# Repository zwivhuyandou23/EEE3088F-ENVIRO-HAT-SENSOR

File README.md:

### ENVIRO-SENSING-HAT

## Name
ENVIRO-SENSING-HAT

## Description

The ENVIRO-SENSING-HAT is a design project that incorporates a Light Dependent Resistor (LDR) and a temperature sensor with an onboard FTDI IC chip. This HAT (Hardware Attached on Top) is designed to provide environmental sensing capabilities for various applications.

## Features

- Light Dependent Resistor (LDR) for monitoring light levels
- Temperature sensor for measuring ambient temperature
- Onboard FTDI IC chip for communication and data transfer
- Customizable and programmable for different applications

## Project Scenarios

The ENVIRO-SENSING-HAT can be used in various scenarios to monitor and analyze environmental conditions. Some of the key scenarios include:

1. **Fire Detection:** The HAT can monitor light levels and temperature. In the case of a fire, the light levels and temperature will rise to extreme levels. The HAT can be integrated into a fire detection system where it triggers an alarm if the levels exceed a certain threshold.

2. **Weather Station:** By monitoring light levels and temperature, the HAT can be used as part of a weather station for weather forecasting purposes. It can collect data over time to analyze weather patterns and provide valuable insights.

3. **Greenhouse Control System:** In a greenhouse, the HAT can be integrated into a control system to monitor environmental conditions. It can detect light levels and temperature to determine the optimal conditions for plant growth. The HAT can control fans and irrigation systems based on the detected environmental conditions.

## Installation
To access some of the contents on the repo you will need kicad to open the project PCB, Schematics designs and an IDE that supports C programming

## Usage

To use the ENVIRO-SENSING-HAT, you need to connect it to a compatible development board or microcontroller. You can refer to the documentation or specifications of your specific board to understand how to interface with the HAT. Additionally, you may need to install any required libraries or drivers for proper functionality.

Once the HAT is properly connected, you can develop software or write code to read data from the LDR and temperature sensor, and utilize the onboard FTDI IC chip for communication and data transfer.

## Authors and acknowledgment

Zwivhuya Ndou, Sivuyile Nose, Talifhani Nemaangani

## Contributing

Contributions to the ENVIRO-SENSING-HAT project are welcome! If you have any ideas, bug fixes, or improvements, please follow the guidelines outlined in the [CONTRIBUTING.md](CONTRIBUTING.md) file.

## License

The ENVIRO-SENSING-HAT project is licensed under the MIT License. See the [LICENSE](LICENSE.md) file for more information.

## Project status
Requirements Identifying

## Contact

If you have any questions or inquiries about the ENVIRO-SENSING-HAT project, feel free to contact us at [CONTACT](Zwivhuya Ndou, Sivuyile Nose, Talifhani Nemaangani).

Thank you for your interest in the ENVIRO-SENSING-HAT project!

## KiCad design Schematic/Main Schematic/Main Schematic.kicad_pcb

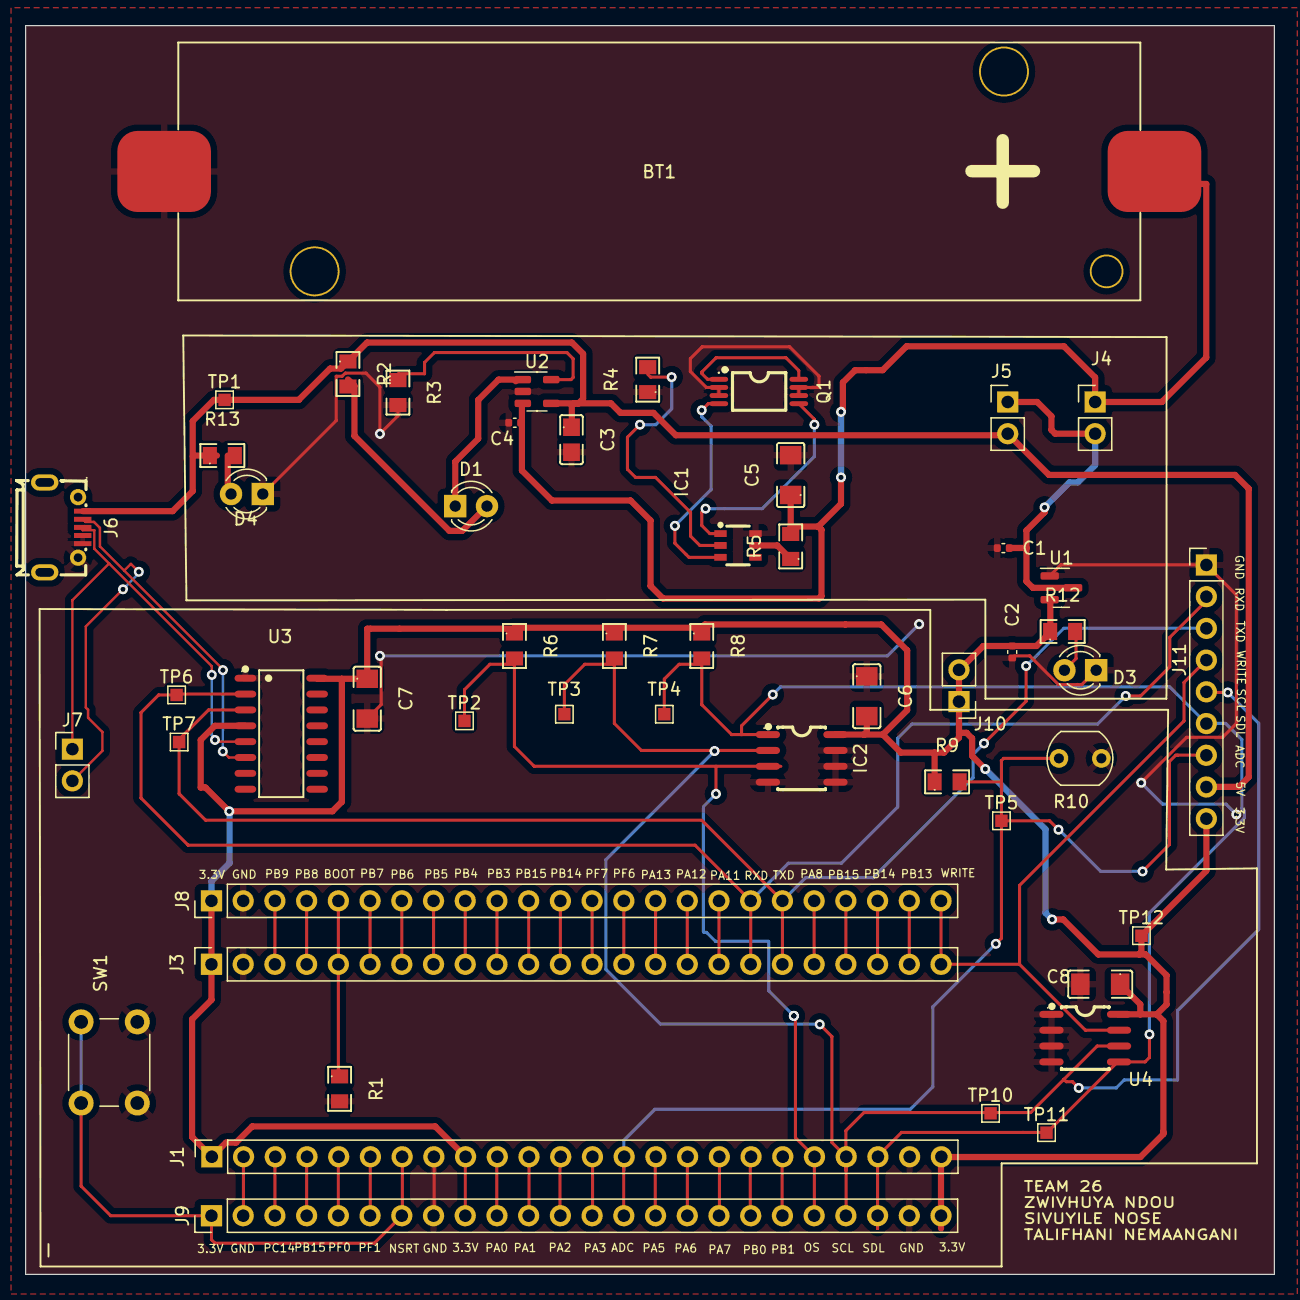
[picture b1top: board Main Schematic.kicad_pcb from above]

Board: 2 copper layers, 100.0 x 100.0 mm, 52 parts (0 on the bottom side), 58 nets.

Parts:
BT1: Battery_Cell; 18650_Holder_SMD
C1, C2: 1uF; C_0402_1005Metric
C3: 4.7uF; C0805
C4: 10uF; C_0402_1005Metric
C5: 100n; C1206
C6: 0.1uF; C1206
C7: 100nF; C1206
C8: 10nF; C1206
D1, D3, D4: LED; LED_D3.0mm
IC1: DW01A-G; SOT-23-6_L2.9-W1.6-P0.95-LS2.8-BR
IC2: LM75AD,118; SOIC-8_L5.0-W4.0-P1.27-LS6.0-BL
J1, J3: Conn_01x24_Socket; PinSocket_1x24_P2.54mm_Vertical
J4, J5: Conn_01x02_Male; PinHeader_1x02_P2.54mm_Vertical
J6: USB_B_Micro; MICRO-USB-SMD_MICROXNJ
J7, J10: Conn_01x02_Pin; PinHeader_1x02_P2.54mm_Vertical
J8, J9: Conn_01x24_Pin; PinHeader_1x24_P2.54mm_Vertical
J11: Conn_01x09_Pin; PinHeader_1x09_P2.54mm_Vertical
Q1: FS8205A; TSSOP-8_L4.4-W3.0-P0.65-LS6.4-BL-2
R1, R6, R7, R8, R9: 10k; R0805
R2, R4: 1K; R0805
R3: 10K; R0805
R5: 100; R0805
R10: LDR07; R_LDR_5.1x4.3mm_P3.4mm_Vertical
R12, R13: 1k; R0805
SW1: SW_Push; SW_PUSH_6mm
TP1: 5V; TestPoint_Pad_1.0x1.0mm
TP2: OS; TestPoint_Pad_1.0x1.0mm
TP3: SCL1; TestPoint_Pad_1.0x1.0mm
TP4: SDA1; TestPoint_Pad_1.0x1.0mm
TP5: TestPoint; TestPoint_Pad_1.0x1.0mm
TP6: RXD testpoint; TestPoint_Pad_1.0x1.0mm
TP7: TXD testpoint; TestPoint_Pad_1.0x1.0mm
TP10: SCL; TestPoint_Pad_1.0x1.0mm
TP11: SDL; TestPoint_Pad_1.0x1.0mm
TP12: 3.3V to EEprom; TestPoint_Pad_1.0x1.0mm
U1: MCP1700x-330xxTT; SOT-23
U2: MCP73831-2-OT; SOT-23-5
U3: CH340C; SOP-16_L10.0-W3.9-P1.27-LS6.0-BL
U4: M24C16-RMN6TP; SOIC-8_L5.0-W4.0-P1.27-LS6.0-BL

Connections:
/3.3V: C2.1, C6.2, C7.1, C8.1, IC2.8 (VCC), J1.1, J1.9, J1.24, J3.1, J8.1, J9.9, J9.24, J10.1, J10.2, J11.9, R6.1, R7.1, R8.1, R9.1, R12.1, TP12.1, U1.2 (VO), U3.4 (V3), U3.16 (VCC), U4.8 (VCC)
/5V: C3.1, J5.2, J6.1 (VBUS), J11.8, R2.1, R13.1, TP1.1, U2.4 (VDD)
/ADC: J1.14, J9.14, J11.7, R9.2, R10.1, TP5.1
/BOOT: J3.5, J8.5, R1.1
/NRST: J1.7, J9.1, J9.7, SW1.2
/OS: IC2.3 (OS), J1.20, J9.20, R6.2, TP2.1
/PA0: J1.10, J9.10
/PA1: J1.11, J9.11
/PA2: J1.12, J9.12
/PA3: J1.13, J9.13
/PA5: J1.15, J9.15
/PA6: J1.16, J9.16
/PA7: J1.17, J9.17
/PA8: J3.20, J8.20
/PA11: J3.17, J8.17
/PA12: J3.16, J8.16
/PA13: J3.15, J8.15
/PA14: J3.12, J8.12
/PA15: J3.11, J8.11
/PB0: J1.18, J9.18
/PB1: J1.19, J9.19
/PB3: J3.10, J8.10
/PB4: J3.9, J8.9
/PB5: J3.8, J8.8
/PB6: J3.7, J8.7
/PB7: J3.6, J8.6
/PB8: J3.4, J8.4
/PB9: J3.3, J8.3
/PB13: J3.23, J8.23
/PB14: J3.22, J8.22
/PB15: J3.21, J8.21
/PC13: J1.2, J9.2
/PC14: J1.3, J9.3
/PC15: J1.4, J9.4
/PF0: J1.5, J9.5
/PF1: J1.6, J9.6
/PF6: J3.14, J8.14
/PF7: J3.13, J8.13
/Power Unit/D12: Q1.1 (D12_1), Q1.8 (D12_2)
/Power Unit/OC: IC1.3 (OC), Q1.4 (G1)
/Power Unit/OD: IC1.1 (OD), Q1.5 (G2)
/Power Unit/V1: BT1.1 (+), C4.1, C5.1, J4.1, R5.2, U2.3 (VBAT)
/RXD: J3.18, J8.18, J11.2, TP6.1, U3.2 (TXD)
/SCL: IC2.2 (SCL), J1.21, J9.21, J11.5, R7.2, TP3.1, TP10.1, U4.6 (SCL)
/SDL: IC2.1 (SDA), J1.22, J9.22, J11.6, R8.2, TP4.1, TP11.1, U4.5 (SDA)
/TXD: J3.19, J8.19, J11.3, TP7.1, U3.3 (RXD)
/USB D+: J6.3 (D+), J7.1, U3.5 (UD+)
/USB D-: J6.2 (D-), J7.2, U3.6 (UD-)
/WRITE: J3.24, J8.24, J11.4, U4.7 (~WC)
GND: BT1.2 (-), C1.2, C2.2, C3.2, C4.2, C5.2, C6.1, C7.2, C8.2, D3.1 (K), D4.1 (K), IC1.6 (GND), IC2.4 (GND), IC2.5 (A2), IC2.6 (A1), IC2.7 (A0), J1.8, J1.23, J3.2, J6.4 (ID), J6.5 (GND), J6.6 (Shield), J8.2, J9.8, J9.23, J11.1, Q1.2 (S1_1), Q1.3 (S1_2), Q1.6 (S2_1), Q1.7 (S2_2), R1.2, R3.2, R4.1, R10.2, SW1.1, U1.1 (GND), U2.2 (VSS), U3.1 (GND), U4.1 (E0), U4.2 (E1), U4.3 (E2), U4.4 (VSS)
unnamed: C1.1, J4.2, J5.1, U1.3 (VI)
unnamed: D1.2 (A), R2.2
unnamed: D1.1 (K), U2.1 (STAT)
unnamed: D3.2 (A), R12.2
unnamed: D4.2 (A), R13.2
unnamed: IC1.2 (CS), R4.2
unnamed: IC1.5 (VCC), R5.1
unnamed: R3.1, U2.5 (PROG)

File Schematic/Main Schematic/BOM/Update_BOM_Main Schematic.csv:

"Id";"Designator";"Footprint";"Quantity";"Designation";"Supplier and ref";
1;"J3,J1";"PinSocket_1x24_P2.54mm_Vertical";2;"Conn_01x24_Socket";;;
2;"UVL_PRO";"SOT-23-6_L2.9-W1.6-P0.95-LS2.8-BR";1;"DW01A-G";;;
3;"J7,J2";"PinHeader_1x02_P2.54mm_Vertical";2;"Conn_01x02_Pin";;;
4;"BT1";"18650_Holder_SMD";1;"Battery_Cell";;;
5;"C6";"C1206";1;"0.1uF";;;
6;"C5";"C1206";1;"100n";;;
7;"TP6";"TestPoint_Pad_1.0x1.0mm";1;"RXD testpoint";;;
8;"C3";"C_0201_0603Metric";1;"4.7uF";;;
9;"C7";"C1206";1;"100nF";;;
10;"BATTERY_CHARGER";"SOT-23-5";1;"MCP73831-2-OT";;;
11;"R9,R7,R1,R8,R6";"R_1206_3216Metric";5;"10k";;;
12;"R2,R4";"R0402";2;"1K";;;
13;"C1,C2";"C_0402_1005Metric";2;"10u";;;
14;"EEPROM";"C1206";1;"10nF";;;
15;"TP13,TP5";"TestPoint_Pad_1.0x1.0mm";2;"TestPoint";;;
16;"U4";"SOIC-8_L5.0-W4.0-P1.27-LS6.0-BL";1;"M24C16-RMN6TP";;;
17;"D3,D4,D1";"LED_D3.0mm";3;"LED";;;
18;"TP10";"TestPoint_Pad_1.0x1.0mm";1;"SCL";;;
19;"J8,J9";"PinHeader_1x24_P2.54mm_Vertical";2;"Conn_01x24_Pin";;;
20;"C4";"C_0402_1005Metric";1;"10uF";;;
21;"TP7";"TestPoint_Pad_1.0x1.0mm";1;"TXD testpoint";;;
22;"TP11";"TestPoint_Pad_1.0x1.0mm";1;"SDL";;;
23;"J4,J5";"PinHeader_1x02_P2.54mm_Vertical";2;"Conn_01x02_Male";;;
24;"R12,R13";"R0402";2;"1k";;;
25;"VOLT-DIV";"SOT-89-3";1;"HT75xx-1-SOT89";;;
26;"TP12";"TestPoint_Pad_1.0x1.0mm";1;"3.3V to EEprom";;;
27;"IC2";"SOIC-8_L5.0-W4.0-P1.27-LS6.0-BL";1;"LM75AD,118";;;
28;"DEBUGGER";"PinHeader_1x09_P2.54mm_Vertical";1;"Conn_01x09_Pin";;;
29;"TP1";"TestPoint_Pad_1.0x1.0mm";1;"5V";;;
30;"TP3";"TestPoint_Pad_1.0x1.0mm";1;"SCL1";;;
31;"R3";"R_1206_3216Metric";1;"10K";;;
32;"TP4";"TestPoint_Pad_1.0x1.0mm";1;"SDA1";;;
33;"Q1";"TSSOP-8_L4.4-W3.0-P0.65-LS6.4-BL-2";1;"FS8205A";;;
34;"R5";"C1206";1;"100";;;
35;"J6";"MICRO-USB-SMD_MICROXNJ";1;"USB_B_Micro";;;
36;"CH340C UART";"SOP-16_L10.0-W3.9-P1.27-LS6.0-BL";1;"CH340C";;;
37;"SW1";"SW_PUSH_6mm";1;"SW_Push";;;
38;"R10";"R_LDR_5.1x4.3mm_P3.4mm_Vertical";1;"LDR07";;;
39;"TP2";"TestPoint_Pad_1.0x1.0mm";1;"OS";;;

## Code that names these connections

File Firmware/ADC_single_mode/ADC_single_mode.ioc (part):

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Mcu.Name=STM32F051C6Tx
Mcu.Package=LQFP48
Mcu.UserName=STM32F051C6Tx
PA10.Mode=Asynchronous
PA10.Signal=USART1_RX
PA4.Mode=IN4
PA4.Signal=ADC_IN4
PA9.Mode=Asynchronous
PA9.Signal=USART1_TX
PB0.Signal=GPIO_Output
PB3.Signal=GPIO_Output
PB5.Signal=GPIO_Output
PB6.Signal=I2C1_SCL
PB7.Signal=I2C1_SDA
board=custom

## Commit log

2023-02-23 Configure SAST in `.gitlab-ci.yml`, creating this file if it does not already exist
2023-02-23 Testing1212
2023-02-24 basic repo
2023-02-24 Some discovery user manuals
2023-02-24 Added EEPROM Demo
2023-02-24 pending
2023-02-24 Production Processes
2023-02-24 Creating readme file
2023-02-24 2nd Update
2023-03-04 Add new directory
2023-03-04 Upload New File
2023-03-06 Sensor Module costs Spreadsheet
2023-03-06 Sensor Module Costs pdf
2023-03-06 Sensor Schematic draft
2023-03-06 added BILL OF MATERIALS and schematic
2023-03-06 BILL OF MATERIALS
2023-03-06 added Bill of materials
2023-03-06 power schematic
2023-03-06 Added Main Schematic
2023-03-06 Power management picture
2023-03-07 deleted the extra sensor module costs sheet
2023-03-07 Added the main schematic the group is working on
2023-03-07 I recreated our schematics into hierachy sheets instead of individual sheets
2023-03-09 Updated the MCU circuit
2023-03-09 Updated the MCU
2023-03-10 I have made the sensor wiring clearer
2023-03-10 updated sche
2023-03-10 I reorganised the folders from pcb to a separate schematics
2023-03-10 I have moved our main schematic and supplementary schematics to the new schematic direactory
2023-03-10 I've edited the main schematic layout
2023-03-10 More edit to the main schematic
2023-03-10 Updated main schematic but not entirely
2023-03-10 'MCU.kicad_sch'
2023-03-10 'Updated'
2023-03-10 'Update'
2023-03-11 I made few comments on the sensing
2023-03-12 I have commented on my module explaining the significant parts
2023-03-12 Sensor comment
2023-03-12 I have updated the power management unit
2023-03-13 I have added net lables and hierachy labels on the main schmeatic
2023-03-13 All pin connections confirmed
2023-03-13 Updatw
2023-03-13 'Reorganised'
2023-03-14 I have updated the power unit schematic
2023-03-15 re organise
2023-03-17 Updat
2023-03-17 assigned footprints for most of the components
2023-03-17 Changed sensor resistors
2023-03-17 Updated sensing R
2023-03-17 Updated the footprints and the PCB
2023-03-17 I Fixed the connections on the power module ,because the jumper was not cinnected properly
2023-03-18 footprints and symbols
2023-03-18 I have removed the old folders of our old schematic
2023-03-18 Footprints all added and the PCB has been created but not placed according to the proper configuration
2023-03-19 Message
2023-03-19 PCB UPDATE
2023-03-19 traces done
2023-03-19 updated the conn connections
2023-03-20 added BOM
2023-03-20 traces
2023-03-20 No change
2023-03-21 I've added the local footprints and gerber files into the repo
2023-03-21 Update BOM
2023-03-23 Removed old csv BOM's
2023-03-23 Added the gnd filling zone, moved decoupling caps close to the IC, ensured no tracks are under and IC
2023-03-23 Edited the ocb nets for uart
2023-03-23 Updated the pcb
2023-03-23 Adjusted the female headers width
2023-03-24 Added conn for sensor
2023-03-24 LED added for visuals
2023-03-25 Added more led for visual indications, also changed debugger pins to 9 pins for 3.3v pin
2023-03-25 Edit
2023-04-03 Added QR code to the B.Silkcreen
2023-04-03 Added the pads value in silkscreen
2023-04-03 QR code
2023-04-03 Added silk screens on the PCB layout board
2023-04-03 Added UCT logo
2023-04-03 Design done
2023-04-03 BOM_POS
2023-04-04 POS files updated
2023-04-04 NEW BOM < POS
2023-04-04 Design part Done
2023-04-13 added new V regulator
2023-04-14 POS_BOM_GERBER updated
2023-04-14 hello
2023-04-22 removed uct logo
2023-04-23 corrected drc and unrouted issues
2023-04-23 Saved new gerber and new pos file
2023-04-24 pcb files all in order and showing perfect on jlcpcb
2023-05-13 Update README.md
    Just added a few things on the read me, still to edit more
2023-05-13 Added code reference, subject to change please go through it
2023-05-17 code
